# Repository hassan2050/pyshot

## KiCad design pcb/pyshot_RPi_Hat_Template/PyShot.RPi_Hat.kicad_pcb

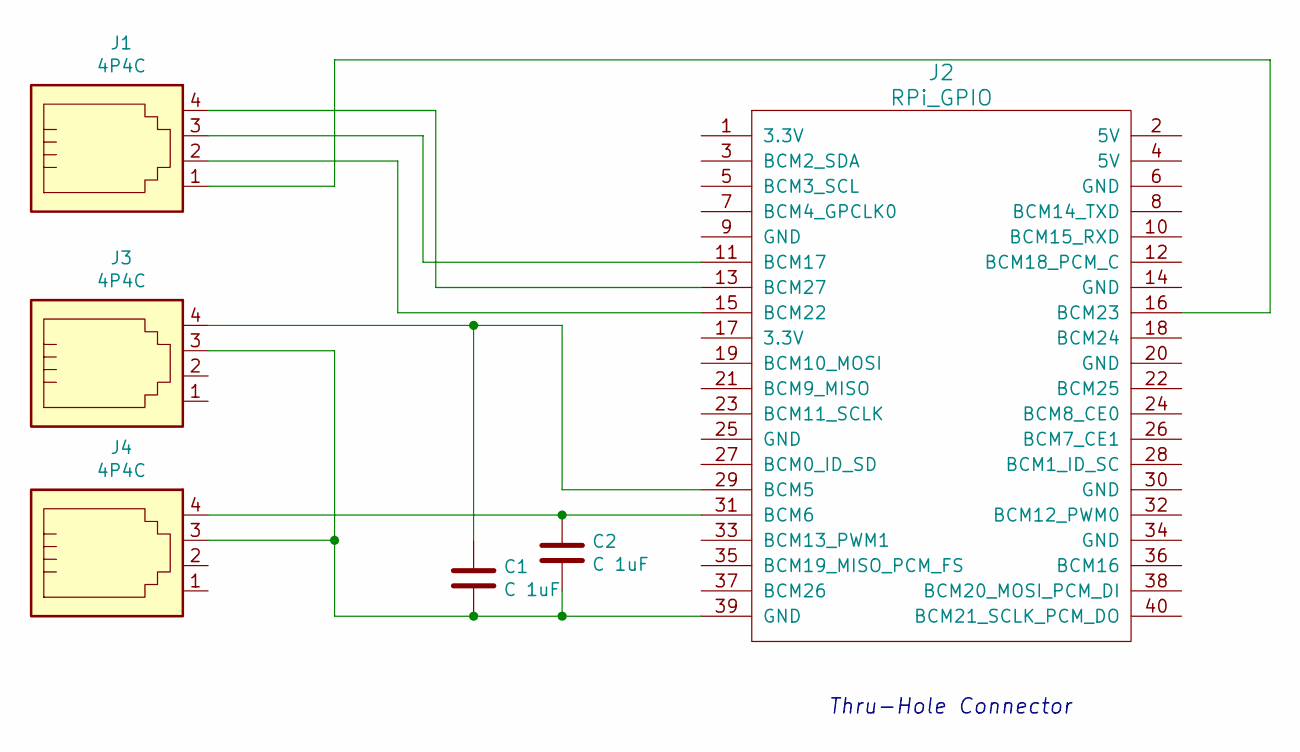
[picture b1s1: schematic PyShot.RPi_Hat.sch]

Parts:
C1, C2: C 1uF; C_Rect_L11.0mm_W3.4mm_P10.00mm_MKT
J1, J3, J4: 4P4C; RJ14_Connfly_DS1133-S4_Horizontal
J2: RPi_GPIO; Pin_Header_Straight_2x20

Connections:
unnamed: C1.1, J2.29 (BCM5), J3.4
unnamed: C1.2, C2.2, J2.39 (GND), J3.3, J4.3
unnamed: C2.1, J2.31 (BCM6), J4.4
unnamed: J1.1, J2.16 (BCM23)
unnamed: J1.2, J2.15 (BCM22)
unnamed: J1.3, J2.11 (BCM17)
unnamed: J1.4, J2.13 (BCM27)

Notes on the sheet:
Thru-Hole Connector

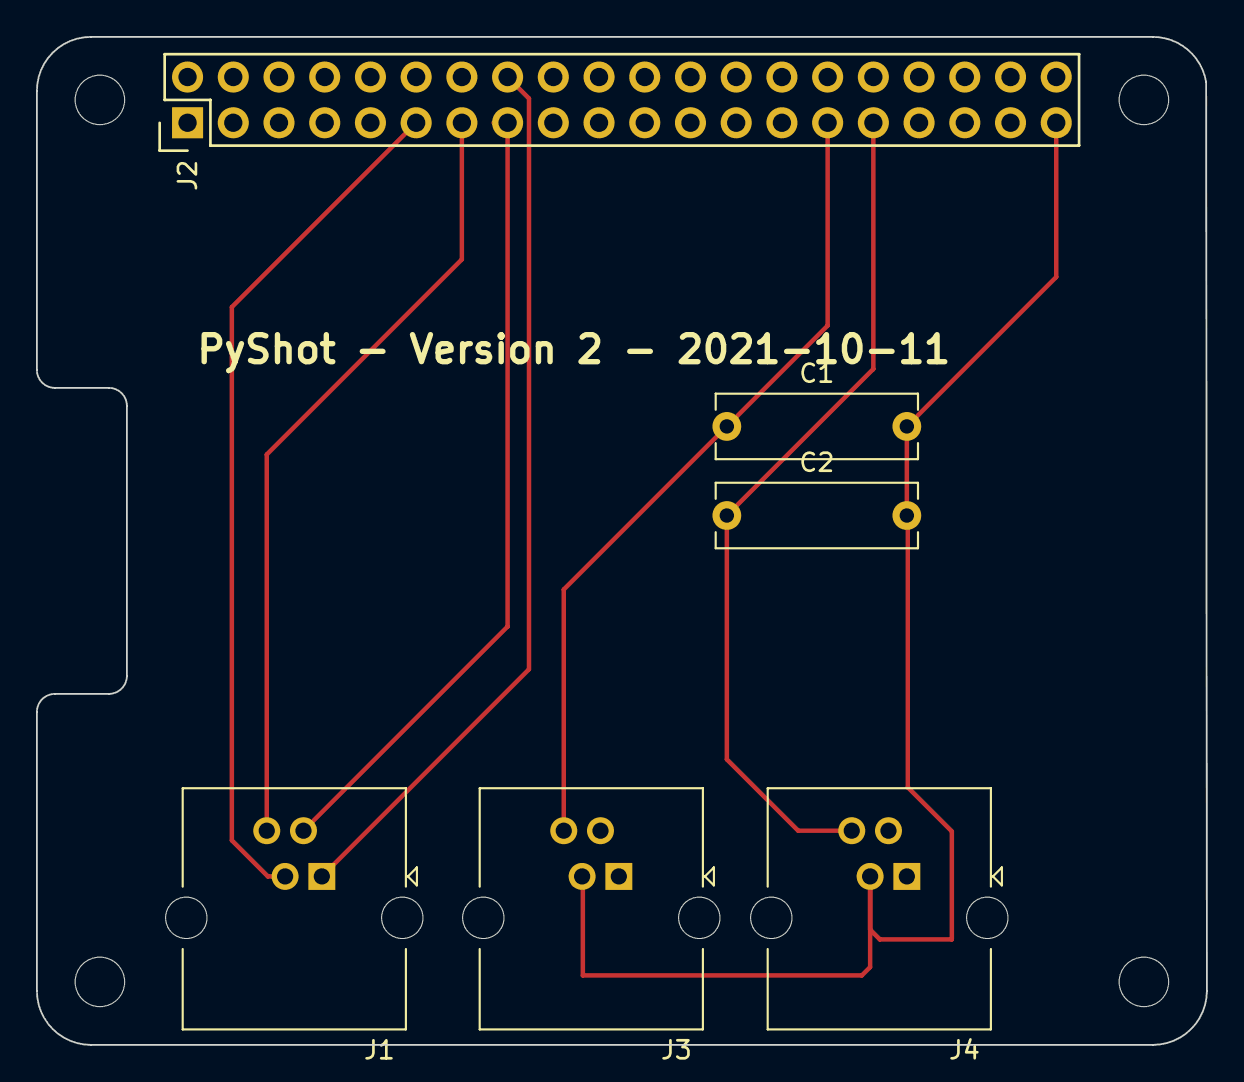
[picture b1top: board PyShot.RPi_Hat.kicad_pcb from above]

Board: 2 copper layers, 65.0 x 56.0 mm, 6 parts (0 on the bottom side), 7 nets.

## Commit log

2021-10-14 initial checkin
2021-10-14 initial
2021-10-15 reorg
2021-10-15 screens
2021-10-15 font
2021-10-17 added pyshot for ursina
2021-10-17 removed background
2021-10-19 enter to start
